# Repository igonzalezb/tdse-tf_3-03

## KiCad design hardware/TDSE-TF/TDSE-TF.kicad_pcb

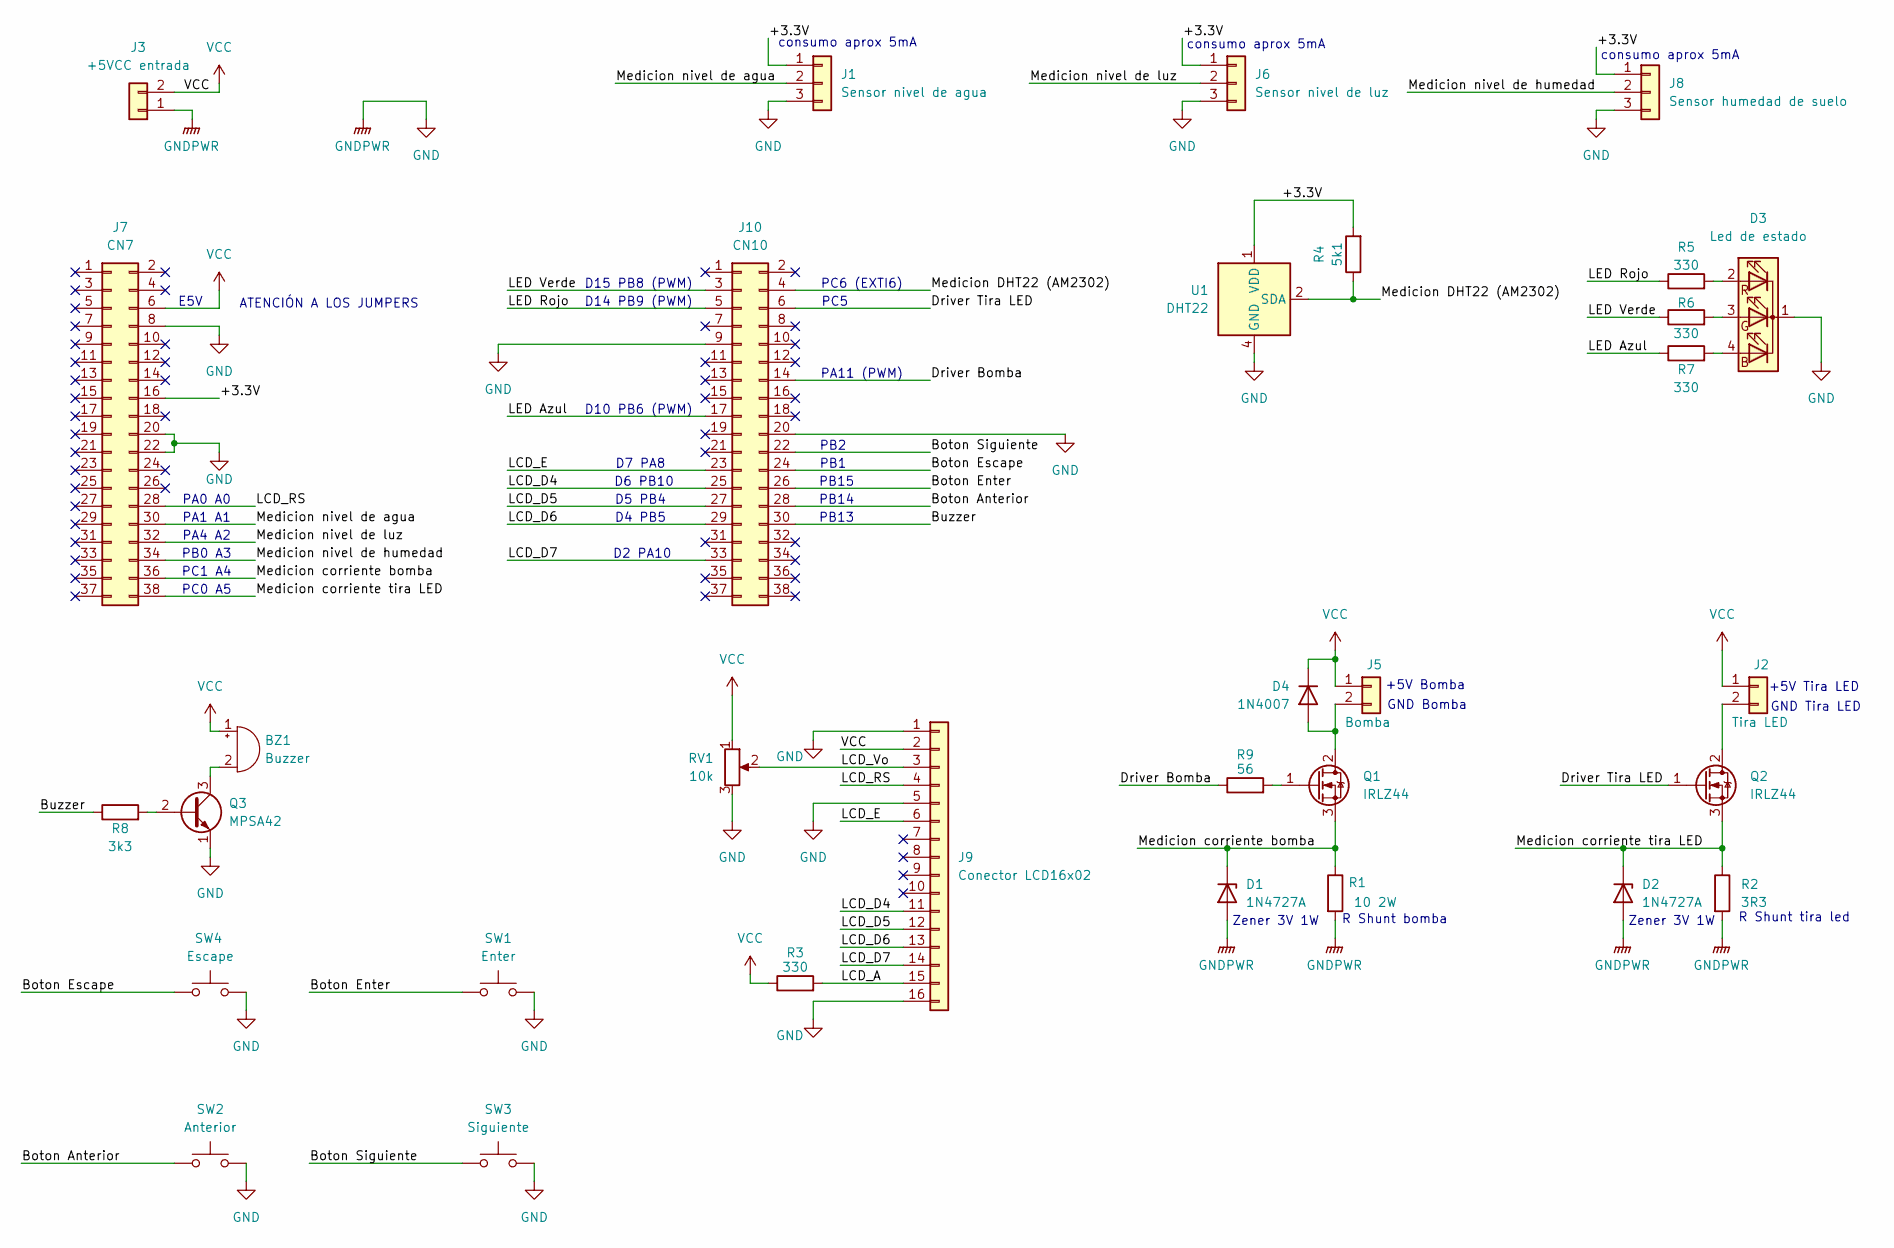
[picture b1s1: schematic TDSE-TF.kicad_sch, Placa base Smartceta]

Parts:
BZ1: Buzzer; Buzzer_12x9.5RM7.6
D1, D2: 1N4727A; D_DO-41_SOD81_P10.16mm_Horizontal
D3: Led de estado; LED_D5.0mm-4_RGB_Wide_Pins
D4: 1N4007; D_DO-41_SOD81_P10.16mm_Horizontal
J1: Sensor nivel de agua; PinHeader_1x03_P2.54mm_Vertical
J2: Tira LED; JST_EH_B2B-EH-A_1x02_P2.50mm_Vertical
J3: +5VCC entrada; JST_EH_B2B-EH-A_1x02_P2.50mm_Vertical
J5: Bomba; JST_EH_B2B-EH-A_1x02_P2.50mm_Vertical
J6: Sensor nivel de luz; PinHeader_1x03_P2.54mm_Vertical
J7: CN7; PinSocket_2x19_P2.54mm_Vertical
J8: Sensor humedad de suelo; PinHeader_1x03_P2.54mm_Vertical
J9: Conector LCD16x02; PinSocket_1x16_P2.54mm_Vertical
J10: CN10; PinSocket_2x19_P2.54mm_Vertical
Q1, Q2: IRLZ44; TO-220-3_Vertical
Q3: MPSA42; TO-92_Inline
R1: 10 2W; R_Axial_DIN0617_L17.0mm_D6.0mm_P25.40mm_Horizontal
R2: 3R3; R_Axial_DIN0617_L17.0mm_D6.0mm_P25.40mm_Horizontal
R3: 330; R_Axial_DIN0207_L6.3mm_D2.5mm_P15.24mm_Horizontal
R4: 5k1; R_Axial_DIN0207_L6.3mm_D2.5mm_P7.62mm_Horizontal
R5, R6, R7: 330; R_Axial_DIN0207_L6.3mm_D2.5mm_P7.62mm_Horizontal
R8: 3k3; R_Axial_DIN0207_L6.3mm_D2.5mm_P7.62mm_Horizontal
R9: 56; R_Axial_DIN0207_L6.3mm_D2.5mm_P10.16mm_Horizontal
RV1: 10k; Potentiometer_Bourns_3386C_Horizontal
SW1: Enter; SW_PUSH_1P1T 2 pines
SW2: Anterior; SW_PUSH_1P1T 2 pines
SW3: Siguiente; SW_PUSH_1P1T 2 pines
SW4: Escape; SW_PUSH_1P1T 2 pines
U1: DHT22; PinSocket_1x04_P2.54mm_Vertical

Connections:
/+3.3V: J1.1, J6.1, J7.16, J8.1, R4.2, U1.1 (VDD)
/Boton Anterior: J10.28, SW2.1
/Boton Enter: J10.26, SW1.1
/Boton Escape: J10.24, SW4.1
/Boton Siguiente: J10.22, SW3.1
/Buzzer: J10.30, R8.1
/Driver Bomba: J10.14, R9.1
/Driver Tira LED: J10.6, Q2.1 (G)
/LCD_A: J9.15, R3.2
/LCD_D4: J9.11, J10.25
/LCD_D5: J9.12, J10.27
/LCD_D6: J9.13, J10.29
/LCD_D7: J9.14, J10.33
/LCD_E: J9.6, J10.23
/LCD_RS: J7.28, J9.4
/LCD_Vo: J9.3, RV1.2
/LED Azul: J10.17, R7.1
/LED Rojo: J10.5, R5.1
/LED Verde: J10.3, R6.1
/Medicion DHT22 (AM2302): J10.4, R4.1, U1.2 (SDA)
/Medicion corriente bomba: D1.1 (K), J7.36, Q1.3 (S), R1.1
/Medicion corriente tira LED: D2.1 (K), J7.38, Q2.3 (S), R2.1
/Medicion nivel de agua: J1.2, J7.30
/Medicion nivel de humedad: J7.34, J8.2
/Medicion nivel de luz: J6.2, J7.32
GND: D1.2 (A), D2.2 (A), D3.1 (K), J1.3, J3.1, J6.3, J7.8, J7.20, J7.22, J8.3, J9.1, J9.5, J9.16, J10.9, J10.20, Q3.1 (E), R1.2, R2.2, RV1.3, SW1.2, SW2.2, SW3.2, SW4.2, U1.4 (GND)
unnamed: BZ1.2 (-), Q3.3 (C)
unnamed: D3.4 (BA), R7.2
unnamed: D3.3 (GA), R6.2
unnamed: D3.2 (RA), R5.2
unnamed: D4.2 (A), J5.2, Q1.2 (D)
unnamed: J2.2, Q2.2 (D)
unnamed: Q1.1 (G), R9.2
unnamed: Q3.2 (B), R8.2
VCC: BZ1.1 (+), D4.1 (K), J2.1, J3.2, J5.1, J7.6, J9.2, R3.1, RV1.1

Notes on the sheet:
D5 PB4
ATENCIÓN A LOS JUMPERS
PB14
PB1
D4 PB5
consumo aprox 5mA
PC5
PC0 A5
PB2
Zener 3V 1W
PA1 A1
PB15
E5V
D14 PB9 (PWM)
D15 PB8 (PWM)
PC1 A4
GND Tira LED
PB0 A3
R Shunt tira led
D2 PA10
PA0 A0
D6 PB10
+5V Bomba
+5V Tira LED
PB13
R Shunt bomba
D10 PB6 (PWM)
D7 PA8
GND Bomba
PA4 A2
PA11 (PWM)
PC6 (EXTI6)

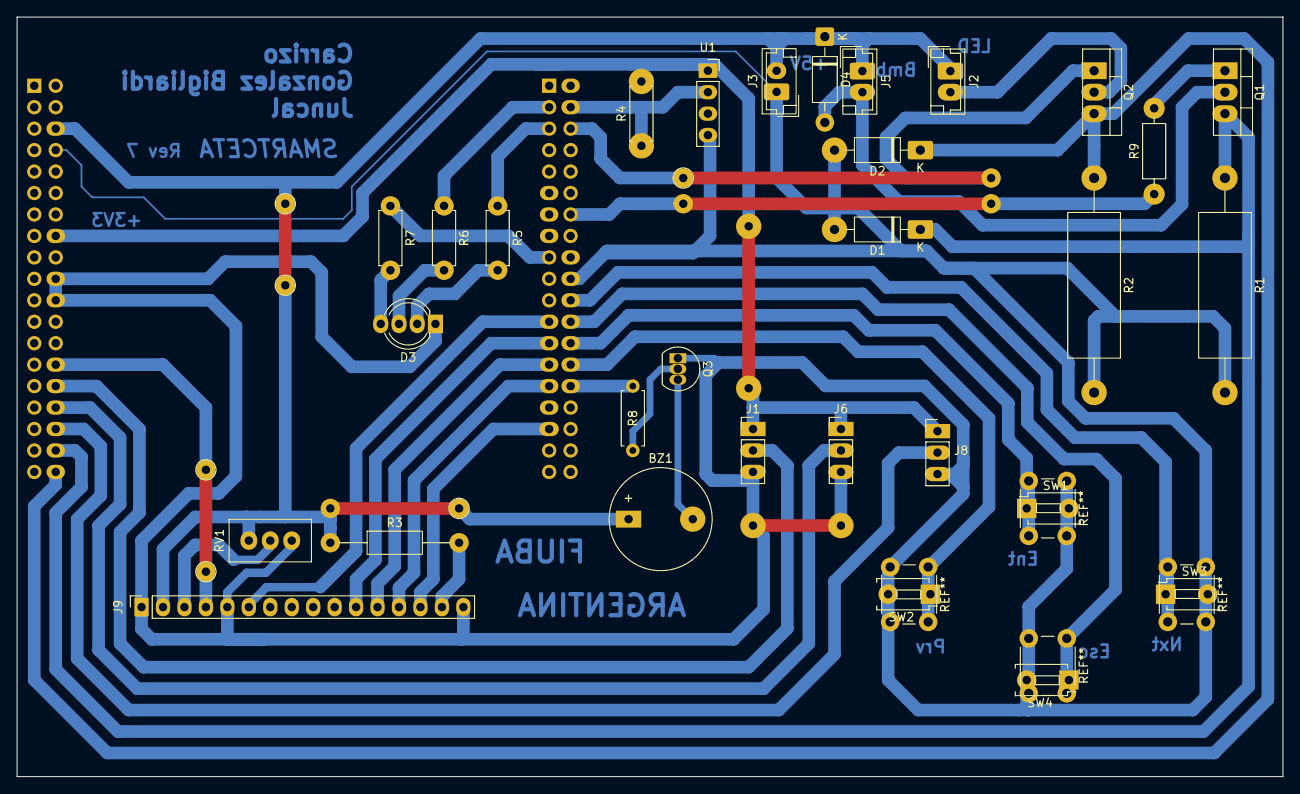
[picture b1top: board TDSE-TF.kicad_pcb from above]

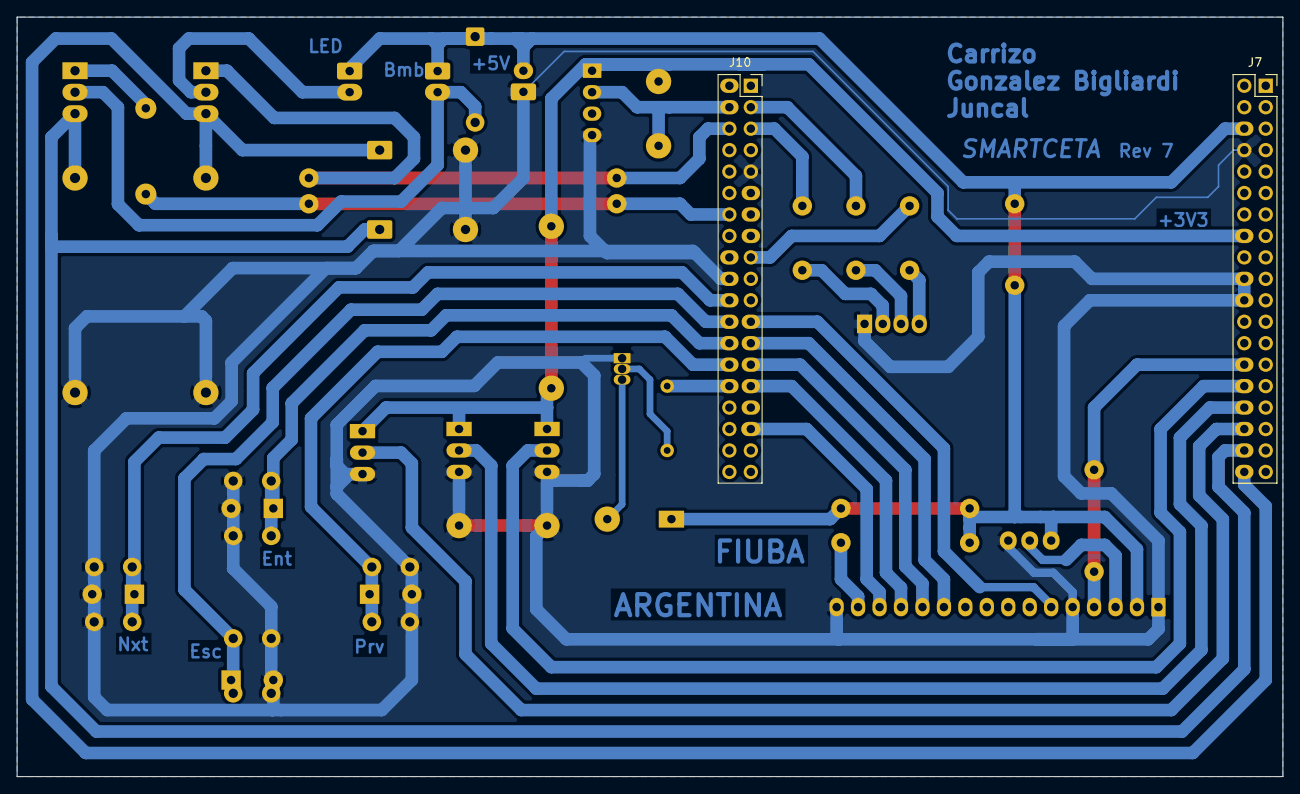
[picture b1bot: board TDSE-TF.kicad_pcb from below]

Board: 2 copper layers, 149.9 x 89.9 mm, 32 parts (2 on the bottom side), 35 nets.

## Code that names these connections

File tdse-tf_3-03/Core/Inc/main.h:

/* USER CODE BEGIN Header */
/**
  ******************************************************************************
  * @file           : main.h
  * @brief          : Header for main.c file.
  *                   This file contains the common defines of the application.
  ******************************************************************************
  * @attention
  *
  * Copyright (c) 2025 STMicroelectronics.
  * All rights reserved.
  *
  * This software is licensed under terms that can be found in the LICENSE file
  * in the root directory of this software component.
  * If no LICENSE file comes with this software, it is provided AS-IS.
  *
  ******************************************************************************
  */
/* USER CODE END Header */

/* Define to prevent recursive inclusion -------------------------------------*/
#ifndef __MAIN_H
#define __MAIN_H

#ifdef __cplusplus
extern "C" {
#endif

/* Includes ------------------------------------------------------------------*/
#include "stm32f1xx_hal.h"

/* Private includes ----------------------------------------------------------*/
/* USER CODE BEGIN Includes */

/* USER CODE END Includes */

/* Exported types ------------------------------------------------------------*/
/* USER CODE BEGIN ET */

/* USER CODE END ET */

/* Exported constants --------------------------------------------------------*/
/* USER CODE BEGIN EC */

/* USER CODE END EC */

/* Exported macro ------------------------------------------------------------*/
/* USER CODE BEGIN EM */

/* USER CODE END EM */

void HAL_TIM_MspPostInit(TIM_HandleTypeDef *htim);

/* Exported functions prototypes ---------------------------------------------*/
void Error_Handler(void);

/* USER CODE BEGIN EFP */

/* USER CODE END EFP */

/* Private defines -----------------------------------------------------------*/
#define B1_Pin GPIO_PIN_13
#define B1_GPIO_Port GPIOC
#define Med_I_LED_Pin GPIO_PIN_0
#define Med_I_LED_GPIO_Port GPIOC
#define Med_I_Bomba_Pin GPIO_PIN_1
#define Med_I_Bomba_GPIO_Port GPIOC
#define LCD_RS_Pin GPIO_PIN_0
#define LCD_RS_GPIO_Port GPIOA
#define S_Nivel_Agua_Pin GPIO_PIN_1
#define S_Nivel_Agua_GPIO_Port GPIOA
#define USART_TX_Pin GPIO_PIN_2
#define USART_TX_GPIO_Port GPIOA
#define USART_RX_Pin GPIO_PIN_3
#define USART_RX_GPIO_Port GPIOA
#define S_Luz_Pin GPIO_PIN_4
#define S_Luz_GPIO_Port GPIOA
#define Tira_LED_Pin GPIO_PIN_5
#define Tira_LED_GPIO_Port GPIOC
#define S_Hum_Suelo_Pin GPIO_PIN_0
#define S_Hum_Suelo_GPIO_Port GPIOB
#define Btn_Esc_Pin GPIO_PIN_1
#define Btn_Esc_GPIO_Port GPIOB
#define Btn_Next_Pin GPIO_PIN_2
#define Btn_Next_GPIO_Port GPIOB
#define LCD_D4_Pin GPIO_PIN_10
#define LCD_D4_GPIO_Port GPIOB
#define Buzzer_Pin GPIO_PIN_13
#define Buzzer_GPIO_Port GPIOB
#define Btn_Prev_Pin GPIO_PIN_14
#define Btn_Prev_GPIO_Port GPIOB
#define Btn_Enter_Pin GPIO_PIN_15
#define Btn_Enter_GPIO_Port GPIOB
#define S_Hum_Temp_Amb_Pin GPIO_PIN_6
#define S_Hum_Temp_Amb_GPIO_Port GPIOC
#define S_Hum_Temp_Amb_EXTI_IRQn EXTI9_5_IRQn
#define LCD_E_Pin GPIO_PIN_8
#define LCD_E_GPIO_Port GPIOA
#define LCD_D7_Pin GPIO_PIN_10
#define LCD_D7_GPIO_Port GPIOA
#define PWM_Bomba_Pin GPIO_PIN_11
#define PWM_Bomba_GPIO_Port GPIOA
#define TMS_Pin GPIO_PIN_13
#define TMS_GPIO_Port GPIOA
#define TCK_Pin GPIO_PIN_14
#define TCK_GPIO_Port GPIOA
#define SWO_Pin GPIO_PIN_3
#define SWO_GPIO_Port GPIOB
#define LCD_D5_Pin GPIO_PIN_4
#define LCD_D5_GPIO_Port GPIOB
#define LCD_D6_Pin GPIO_PIN_5
#define LCD_D6_GPIO_Port GPIOB
#define PWM_LED_B_Pin GPIO_PIN_6
#define PWM_LED_B_GPIO_Port GPIOB
#define PWM_LED_G_Pin GPIO_PIN_8
#define PWM_LED_G_GPIO_Port GPIOB
#define PWM_LED_R_Pin GPIO_PIN_9
#define PWM_LED_R_GPIO_Port GPIOB

/* USER CODE BEGIN Private defines */

/* USER CODE END Private defines */

#ifdef __cplusplus
}
#endif

#endif /* __MAIN_H */

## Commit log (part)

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2025-11-07 Add team members to README
2025-11-07 Requisitos del proyecto: Smartceta
    Se añadieron los requisitos y especificaciones detallados del proyecto Smartceta, incluyendo objetivos, resultados esperados, variantes del proyecto, componentes de hardware y modos operativos.
2025-11-14 Se realizaron las correcciones sugeridas.
2026-01-30 actualizacion estado de avance smartceta
2026-03-04 Primera version del menu interactivo (del TP viejo)
2026-03-05 init varios sistemas
    Primera implementacion de los varios sistemas. Faltaria completar todos los statecharts y ver si compila.
2026-04-10 Saco carpeta inecesaria
2026-04-10 Agregados esquematicos
    Pinera pantalla LCD
    LED RGB (verificar polaridad)
2026-04-10 Menu: Setup & Test
    Primeras versiones de los statecharts de Setup & Test. Hay varios errores y faltan cosas
2026-04-14 Cambios en el esquemático del circuito
    Se reemplazó el MCU por las pineras de la placa
    Se terminaron varias conexiones (LCD, Sensores, Driver tira LED)
    Se emprolijó todo y se añadieron algunas anotaciones en texto
2026-04-21 Primer borrador del menu normal
2026-04-21 Cambio de formato de texto
2026-04-21 Finalizada primera versión de circuito esquematico
2026-04-28 tasks_sensores
    Agrego los .h y .c de los 5 sensores que usen el adc
2026-04-28 Revert "Delete tdse-tf_3-03 directory"
    This reverts commit 81e37a2edce359770deaa7c7ec0f065624469599.
2026-04-28 Add entries to ignore specific metadata files
2026-04-28 Update gitingoner
2026-05-19 compila: union sensores con menu
2026-05-19 Del: archivos viejos
2026-05-26 Finalizados esquema y placa
    Se completó el diseño del circuito esquemático y de la placa asociada al proyecto.
2026-05-28 DHT22
    Agrego el sensor de humedad y temperatura ambiente dht22
2026-05-28 Cambio de pines
    Cambiamos los pines de lugar y agregamos nuevos
2026-05-28 Agrego pull up a botones
2026-05-29 Circuito final - Rev2
    Revisión 2 del circuito esquemático y del PCB.
    Cambios en conexiones del LCD.
    Ajustes de Capa FFab.
    Adjunto nota sobre configuración de jumpres y orden de conexionado de la placa.
2026-05-29 feat: guardado en memoria config & fix: botones y menus
    Guardado en memoria los valores de configuracion de setup. Falta probarlo bien sin Debug.
2026-06-02 Ignore and remove tdse-tf_3-03.cfg
    Remove tdse-tf_3-03/tdse-tf_3-03.cfg from the repo and add it to .gitignore. The config file (generated by STM32CubeIDE) was deleted and its path appended to .gitignore to prevent re-committing gener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
2026-06-02 PCB final Rev 2
    Corregido conexionado de LCD.
2026-06-03 PCB final Rev 3
    Mejorados detalles del PCB y serigrafía
    Añadida opcion de agregar un pullup para el dht22
    Modificado el .ioc
    Creado task_state_led.h (no terminado)
2026-06-05 PCB final Rev 4 y agregado led de estado RGB
    Agregó la lógica de LED RGB de estado con PWM
    Se mejoró el PCB y se incorporaron fichas de conexión mejores para alimentacion y cargas
2026-06-05 PCB final Rev 5 y buzzer
    Se añadió la funcionalidad de buzzer al código
    Se añadió un transistor como driver par el buzzer
    Se actualizó el PCB
2026-06-09 fix: warning de compilacion
2026-06-09 Update app.h
    agrego a shared data el active system.
2026-06-09 Update task_menu.c
    active system en shared data
2026-06-09 Add active_test and TEST_NONE enum
    Add shared_data.active_test to app shared data so the currently selected test can be stored. Update task_menu_test_t: add a trailing comma after TEST_QTY and add TEST_NONE sentinel. Add a TODO commen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
2026-06-09 Ignore and remove IDE launch file
    Add tdse-tf_3-03/tdse-tf_3-03.launch to .gitignore and delete the IDE-specific launch configuration file. This removes a user/IDE-specific STM32Cube/Eclipse launch file from the repository to avoid c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
2026-06-09 Cambio de variable de valores de ADC
2026-06-09 Fix: boton derecho & cambio nombres de test
2026-06-09 task_sensor a task_button
2026-06-10 Arreglado buzzer y LED RGB
    Eliminadas estructuras sobrantes de app.h
    Arreglada lógicas de buzzer y de state_led
    Agregado pinout de NUCLEO-F103RB
2026-06-10 Buzzer en logica de eventos (state led pendiente)
    Se adapto el codigo del buzzer a logica de eventos para actuadores
    El control del led de estado aun está pendiente
    NO MERGEAR
2026-06-11 finalizado buzzer y led en logica de eventos
2026-06-11 Fix linea equivocada
    Se eliminó una linea extra de pruebas que ingresaba al modo falla directamente
2026-06-12 finalizado actuador bomba
    Se implementó una rampa de arranque suave para la bomba
    Se mejoró la estructura de task_buzzer.c
    Ahora se pueden añadir patrones de manera más sencilla
2026-06-12 PCB final Rev 6
    Se añadió compatibilidad con botones de 4 patitas
2026-06-12 Finalizado controlador de tira led
2026-06-16 Add configurable menu & sensors display
    Introduce a new configurable menu flow and refactor task_menu behavior:
    - Add task_menu_config_t enum and current_config field to task_menu_dta_t.
    - Pass shared_data pointer into task_menu via app.c task list.
    - Replace old parameter-based navigation with separate config/navigation state: auto-scroll, pump and light periodic checks (new timers).
    - Add config arrays (config_values, MAX_VAL, MIN_VAL) and config_names initialization.
    - Implement get_sensor_value() to format sensor values for LCD from shared_data.
2026-06-16 Cambios en ubicacion de estructuras de actuadores
    Se movieron los patrones de los actuadores a sus respectivos .c
2026-06-16 Elimino adc value y agrego porcentajes en shared data
2026-06-16 Enhance menu: auto-controls and actuator feedback
    Add pump_on state and initialize current_value. Fix auto-scroll parameter increment. Implement automatic actuator control logic: LED strip on/off based on light config, pump on/off based on water/hum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
2026-06-16 Respect CONFIG_SOUNDS before triggering buzzer
    Guard buzzer actuator calls in task_menu.c behind config_values[CONFIG_SOUNDS] checks. Replaces unconditional put_event_task_actuator(... EV_BUZZER_*) calls with conditional expressions so buzzer eve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
2026-06-16 Cambio pin DHT22
2026-06-16 Remove unused active_test field from shared_data
    Remove the unused `task_menu_test_t active_test;` member from the shared_data_type struct in tdse-tf_3-03/app/inc/app.h. Cleans up the shared data structure and reduces unnecessary memory footprint.
2026-06-16 Improve test-mode actions and menu cleanup
    Add explicit actuator on/off handling for test entries/exits and clean up menu state handling. Removed initialization of shared_data.active_test, switched to using p_task_menu_dta->current_test for t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
2026-06-19 Initialize buzzer and state LED in task_menu
    Trigger startup actuator events in task_menu_init: emit a single buzzer pulse when CONFIG_SOUNDS is enabled and set the state LED to SYS_NORMAL. These additions ensure audible feedback (if configured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
2026-06-20 elimino polling y agrego interrupciones de adc
    Cada vez que el adc interrumpe para entergar el valor del adc, se deriva a la funcion router y se entrega al sensor correspondiente
2026-06-22 Fix auto-scroll parameter boundary check
    Corrects the wrap condition in task_menu_statechart_normal: compare current_parameter against (PARAM_QTY-1) instead of PARAM_QTY to avoid stepping past the last valid parameter index during auto-scro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
2026-06-23 Reorder task menu initializations
2026-06-23 Corrección buzzer en modo test
2026-06-23 Refactor config storage to slot-based flash and UI fixes
    Migrate configuration storage to a slot-based flash layout (4-byte slots: [index, value]) and add helpers to load/save elements. Define page/slot sizes and MAX_SLOTS, implement config_load_from_flash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
2026-06-23 Adjust init behavior
    Initialize last_scroll_tick on menu init and adjust water-level constraints and defaults. Set MIN_VAL[CONFIG_WATER_LEVEL] from 0 to 15, change flash default for CONFIG_WATER_LEVEL from 60 to 40, and 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
2026-06-23 Incluyo evento de falla general y flag para las fallas de pum current, led current y water level
2026-06-23 Use single task_menu_dta instance instead of array
    Replace the task_menu_dta_list array and MENU_DTA_QTY with a single task_menu_dta instance. Update statechart functions to reference &task_menu_dta instead of indexing by shared_data.active_system. T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
2026-06-23 Add non-blocking display task and integrate LCD API
    Introduce a dedicated non-blocking display task: add task_display.h and task_display.c implementing an FSM that streams one LCD character per scheduler tick, uses double buffers (vram_waiting/vram_ac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
2026-06-26 feat: mostrar on/off en config(sounds)
    Muestra ON y OFF en vez de 1/0 en la pantalla LCD cuando se configurar los sonidos.
2026-06-26 Update task_menu.c
    al aumentar/ disminuir los valores de configuracion y llegar a los limites en vez de quedar fijo vuelven a dar la vuelta
2026-06-30 Finalizado modo falla y actualizacion de PCB
    Se terminó el modo falla
    Se ajustaron tamaños y ubicaciones de etiquetas para el FFab del PCB y se corrigió la ubicacion del DHT22
